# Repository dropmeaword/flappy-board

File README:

## Flappy board

(cc) 2017 Jelle Reith + Luis Rodil-Fernandez

Flappy board can be used to drive electromagnets for flappy textile projects.  :)

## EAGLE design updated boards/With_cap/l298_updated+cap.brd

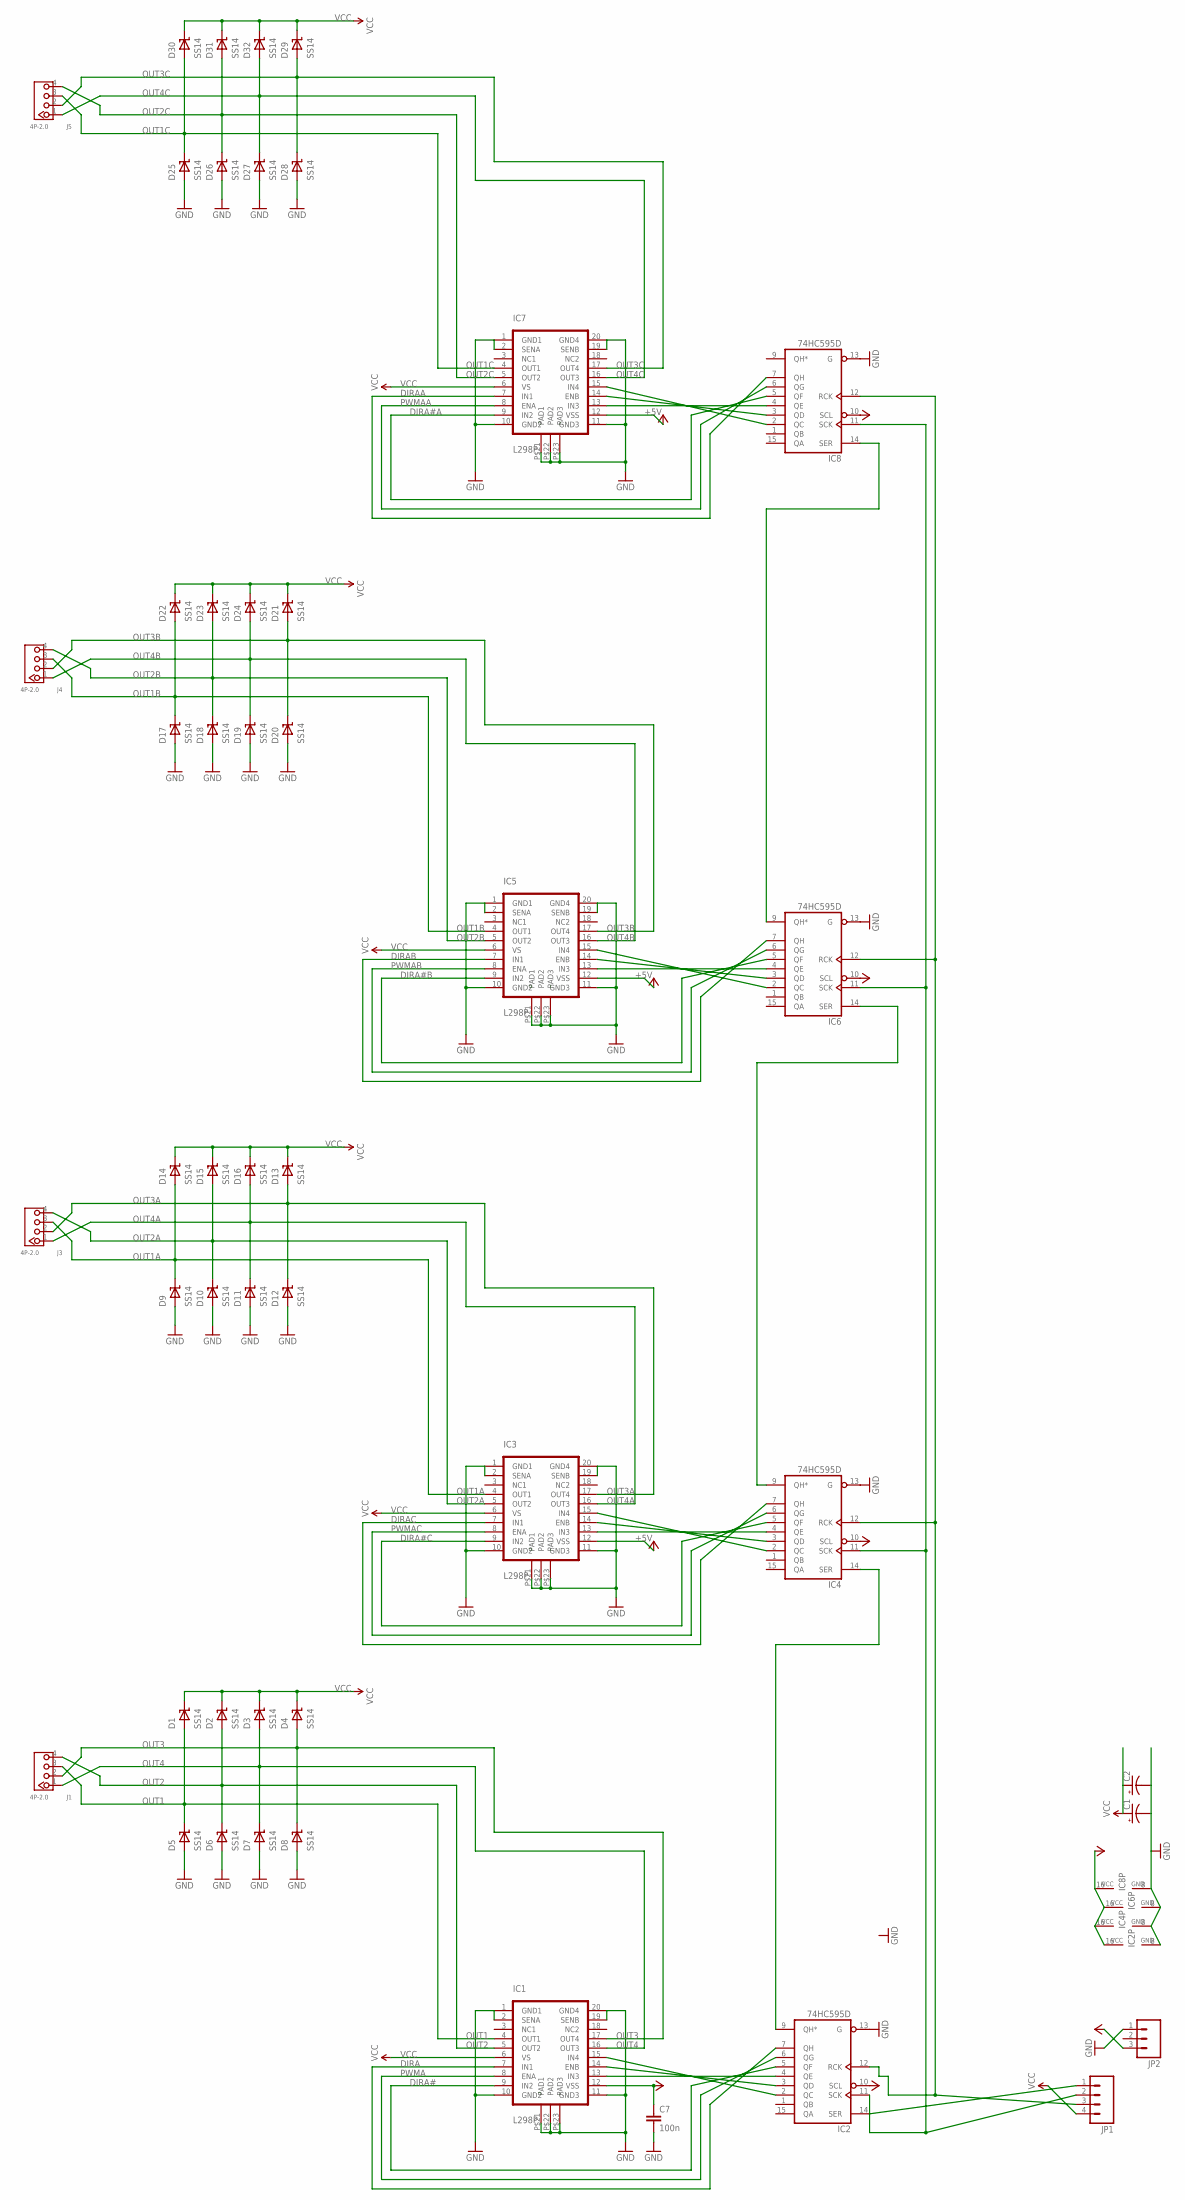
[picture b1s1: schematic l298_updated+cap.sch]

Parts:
C1: CAP_POL1206; EIA3216
C2: CAP_POL3528; EIA3528
C7: 100n; C0603-ROUND
D1, D2, D3, D4, D5, D6, D7, D8, D9, D10, D11, D12, D13, D14, D15, D16, D17, D18, D19, D20, D21, D22, D23, D24, D25, D26, D27, D28, D29, D30, D31, D32: SS14; SMA
IC1, IC3, IC5, IC7: L298P; POWER-SO20
IC2, IC4, IC6, IC8: 74HC595D; SO16
J1, J3, J4, J5: 4P-2.0; HW4-2.0
JP1: M04PTH; 1X04
JP2: M03PTH; 1X03

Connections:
+5V: C7.1, IC1.P$12 (VSS), IC2.10 (SCL), IC2.16 (VCC), IC3.P$12 (VSS), IC4.10 (SCL), IC4.16 (VCC), IC5.P$12 (VSS), IC6.10 (SCL), IC6.16 (VCC), IC7.P$12 (VSS), IC8.10 (SCL), IC8.16 (VCC), JP2.3
DIRA: IC1.P$7 (IN1), IC2.7 (QH)
DIRA#: IC1.P$9 (IN2), IC2.5 (QF)
DIRA#A: IC7.P$9 (IN2), IC8.5 (QF)
DIRA#B: IC5.P$9 (IN2), IC6.5 (QF)
DIRA#C: IC3.P$9 (IN2), IC4.5 (QF)
DIRAA: IC7.P$7 (IN1), IC8.7 (QH)
DIRAB: IC5.P$7 (IN1), IC6.7 (QH)
DIRAC: IC3.P$7 (IN1), IC4.7 (QH)
GND: C1.C (-), C2.C (-), C7.2, D5.P$2 (A), D6.P$2 (A), D7.P$2 (A), D8.P$2 (A), D9.P$2 (A), D10.P$2 (A), D11.P$2 (A), D12.P$2 (A), D17.P$2 (A), D18.P$2 (A), D19.P$2 (A), D20.P$2 (A), D25.P$2 (A), D26.P$2 (A), D27.P$2 (A), D28.P$2 (A), IC1.P$1 (GND1), IC1.P$2 (SENA), IC1.P$10 (GND2), IC1.P$11 (GND3), IC1.P$19 (SENB), IC1.P$20 (GND4), IC1.P$21 (PAD1), IC1.P$22 (PAD2), IC1.P$23 (PAD3), IC2.8 (GND), IC2.13 (G), IC3.P$1 (GND1), IC3.P$2 (SENA), IC3.P$10 (GND2), IC3.P$11 (GND3), IC3.P$19 (SENB), IC3.P$20 (GND4), IC3.P$21 (PAD1), IC3.P$22 (PAD2), IC3.P$23 (PAD3), IC4.8 (GND), IC4.13 (G), IC5.P$1 (GND1), IC5.P$2 (SENA), IC5.P$10 (GND2), IC5.P$11 (GND3), IC5.P$19 (SENB), IC5.P$20 (GND4), IC5.P$21 (PAD1), IC5.P$22 (PAD2), IC5.P$23 (PAD3), IC6.8 (GND), IC6.13 (G), IC7.P$1 (GND1), IC7.P$2 (SENA), IC7.P$10 (GND2), IC7.P$11 (GND3), IC7.P$19 (SENB), IC7.P$20 (GND4), IC7.P$21 (PAD1), IC7.P$22 (PAD2), IC7.P$23 (PAD3), IC8.8 (GND), IC8.13 (G), JP2.1
unnamed: IC2.9 (QH*), IC4.14 (SER)
unnamed: IC4.9 (QH*), IC6.14 (SER)
unnamed: IC6.9 (QH*), IC8.14 (SER)
unnamed: IC1.P$13 (IN3), IC2.4 (QE)
unnamed: IC1.P$14 (ENB), IC2.3 (QD)
unnamed: IC2.14 (SER), JP1.1
unnamed: IC2.11 (SCK), IC4.11 (SCK), IC6.11 (SCK), IC8.11 (SCK), JP1.2
unnamed: IC2.12 (RCK), IC4.12 (RCK), IC6.12 (RCK), IC8.12 (RCK), JP1.3
unnamed: IC1.P$15 (IN4), IC2.2 (QC)
unnamed: IC3.P$13 (IN3), IC4.4 (QE)
unnamed: IC3.P$14 (ENB), IC4.3 (QD)
unnamed: IC3.P$15 (IN4), IC4.2 (QC)
unnamed: IC5.P$13 (IN3), IC6.4 (QE)
unnamed: IC5.P$14 (ENB), IC6.3 (QD)
unnamed: IC5.P$15 (IN4), IC6.2 (QC)
unnamed: IC7.P$13 (IN3), IC8.4 (QE)
unnamed: IC7.P$14 (ENB), IC8.3 (QD)
unnamed: IC7.P$15 (IN4), IC8.2 (QC)
OUT1: D1.P$2 (A), D5.P$1 (K), IC1.P$4 (OUT1), J1.3
OUT1A: D9.P$1 (K), D14.P$2 (A), IC3.P$4 (OUT1), J3.3
OUT1B: D17.P$1 (K), D22.P$2 (A), IC5.P$4 (OUT1), J4.3
OUT1C: D25.P$1 (K), D30.P$2 (A), IC7.P$4 (OUT1), J5.3
OUT2: D2.P$2 (A), D6.P$1 (K), IC1.P$5 (OUT2), J1.4
OUT2A: D10.P$1 (K), D15.P$2 (A), IC3.P$5 (OUT2), J3.4
OUT2B: D18.P$1 (K), D23.P$2 (A), IC5.P$5 (OUT2), J4.4
OUT2C: D26.P$1 (K), D31.P$2 (A), IC7.P$5 (OUT2), J5.4
OUT3: D4.P$2 (A), D8.P$1 (K), IC1.P$17 (OUT4), J1.2
OUT3A: D12.P$1 (K), D13.P$2 (A), IC3.P$17 (OUT4), J3.2
OUT3B: D20.P$1 (K), D21.P$2 (A), IC5.P$17 (OUT4), J4.2
OUT3C: D28.P$1 (K), D29.P$2 (A), IC7.P$17 (OUT4), J5.2
OUT4: D3.P$2 (A), D7.P$1 (K), IC1.P$16 (OUT3), J1.1
OUT4A: D11.P$1 (K), D16.P$2 (A), IC3.P$16 (OUT3), J3.1
OUT4B: D19.P$1 (K), D24.P$2 (A), IC5.P$16 (OUT3), J4.1
OUT4C: D27.P$1 (K), D32.P$2 (A), IC7.P$16 (OUT3), J5.1
PWMA: IC1.P$8 (ENA), IC2.6 (QG)
PWMAA: IC7.P$8 (ENA), IC8.6 (QG)
PWMAB: IC5.P$8 (ENA), IC6.6 (QG)
PWMAC: IC3.P$8 (ENA), IC4.6 (QG)
VCC: C1.A (+), C2.A (+), D1.P$1 (K), D2.P$1 (K), D3.P$1 (K), D4.P$1 (K), D13.P$1 (K), D14.P$1 (K), D15.P$1 (K), D16.P$1 (K), D21.P$1 (K), D22.P$1 (K), D23.P$1 (K), D24.P$1 (K), D29.P$1 (K), D30.P$1 (K), D31.P$1 (K), D32.P$1 (K), IC1.P$6 (VS), IC3.P$6 (VS), IC5.P$6 (VS), IC7.P$6 (VS), JP1.4

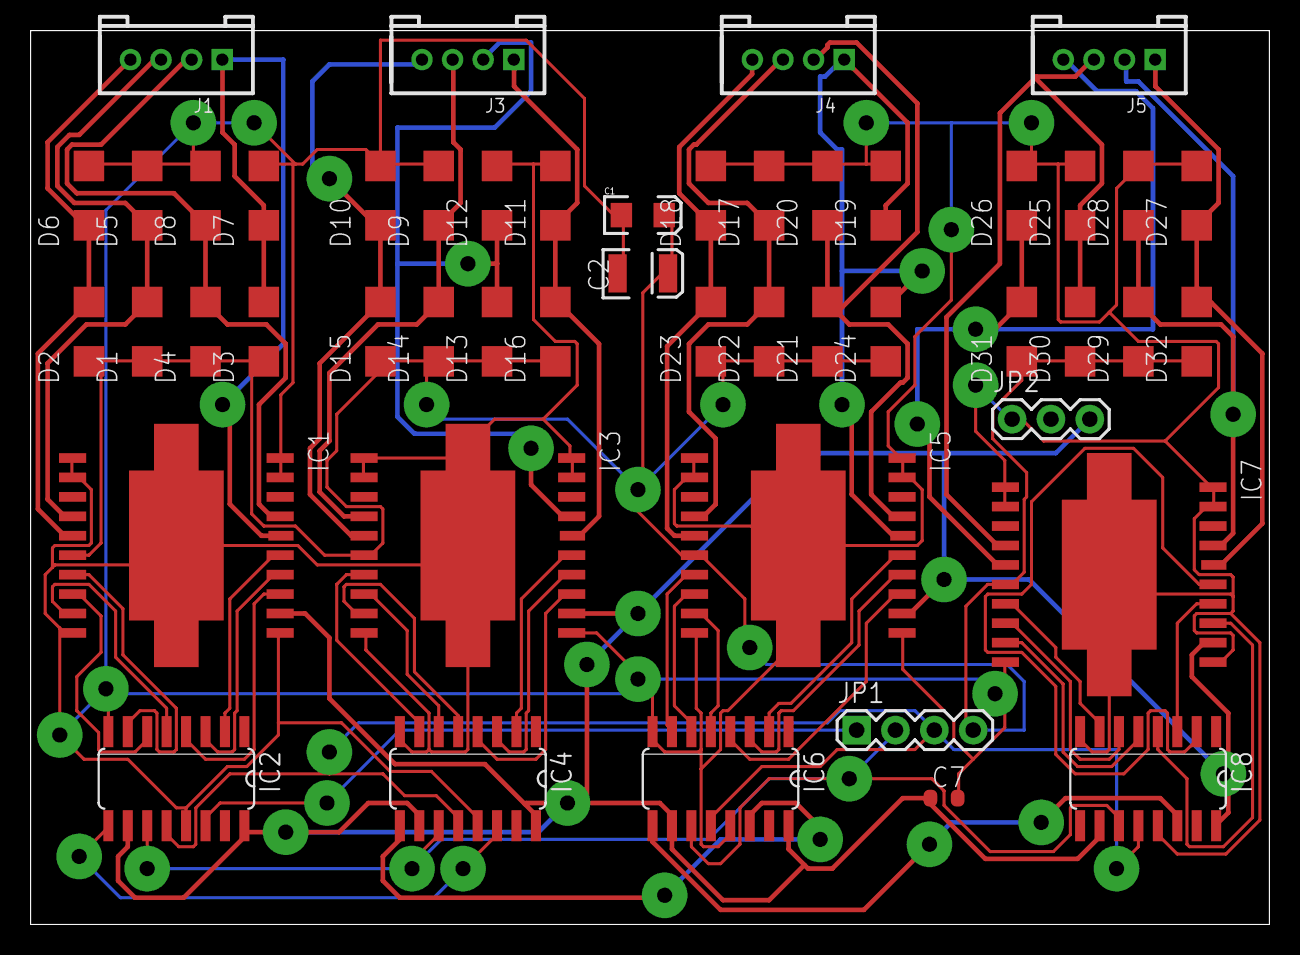
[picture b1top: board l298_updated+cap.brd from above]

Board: 2 copper layers, 81.0 x 58.4 mm, 49 parts (0 on the bottom side), 49 nets.

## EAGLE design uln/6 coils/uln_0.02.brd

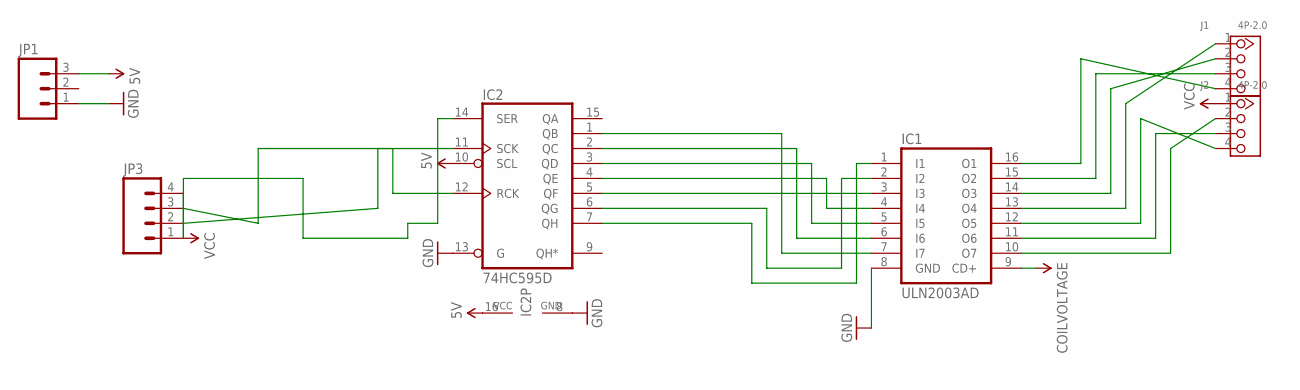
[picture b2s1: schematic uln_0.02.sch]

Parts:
IC1: ULN2003AD; SO16
IC2: 74HC595D; SO16
J1, J2: 4P-2.0; HW4-2.0
JP1: M03PTH; 1X03
JP3: M04PTH; 1X04

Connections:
5V: IC2.10 (SCL), IC2.16 (VCC), JP1.3
GND: IC1.8 (GND), IC2.8 (GND), IC2.13 (G), JP1.1
unnamed: IC1.7 (I7), IC2.1 (QB)
unnamed: IC1.6 (I6), IC2.2 (QC)
unnamed: IC1.5 (I5), IC2.3 (QD)
unnamed: IC1.4 (I4), IC2.4 (QE)
unnamed: IC1.3 (I3), IC2.5 (QF)
unnamed: IC1.2 (I2), IC2.6 (QG)
unnamed: IC1.1 (I1), IC2.7 (QH)
unnamed: IC1.10 (O7), J2.2
unnamed: IC1.11 (O6), J2.3
unnamed: IC1.12 (O5), J2.4
unnamed: IC1.13 (O4), J1.1
unnamed: IC1.14 (O3), J1.2
unnamed: IC1.15 (O2), J1.3
unnamed: IC1.16 (O1), J1.4
unnamed: IC2.11 (SCK), JP3.3
unnamed: IC2.12 (RCK), JP3.2
unnamed: IC2.14 (SER), JP3.1
VCC: IC1.9 (CD+), J2.1, JP3.4

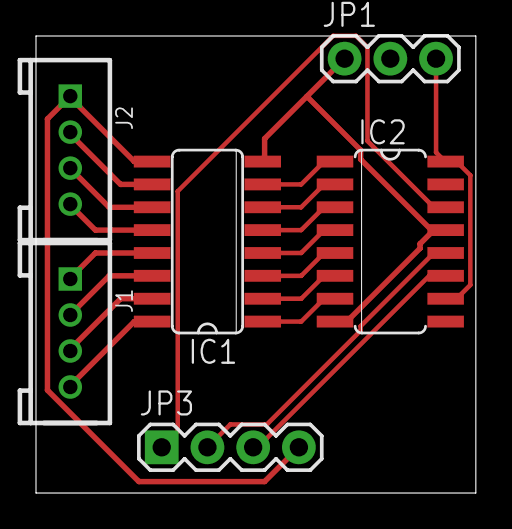
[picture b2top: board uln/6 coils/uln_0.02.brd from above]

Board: 2 copper layers, 24.4 x 25.4 mm, 6 parts (0 on the bottom side), 20 nets.

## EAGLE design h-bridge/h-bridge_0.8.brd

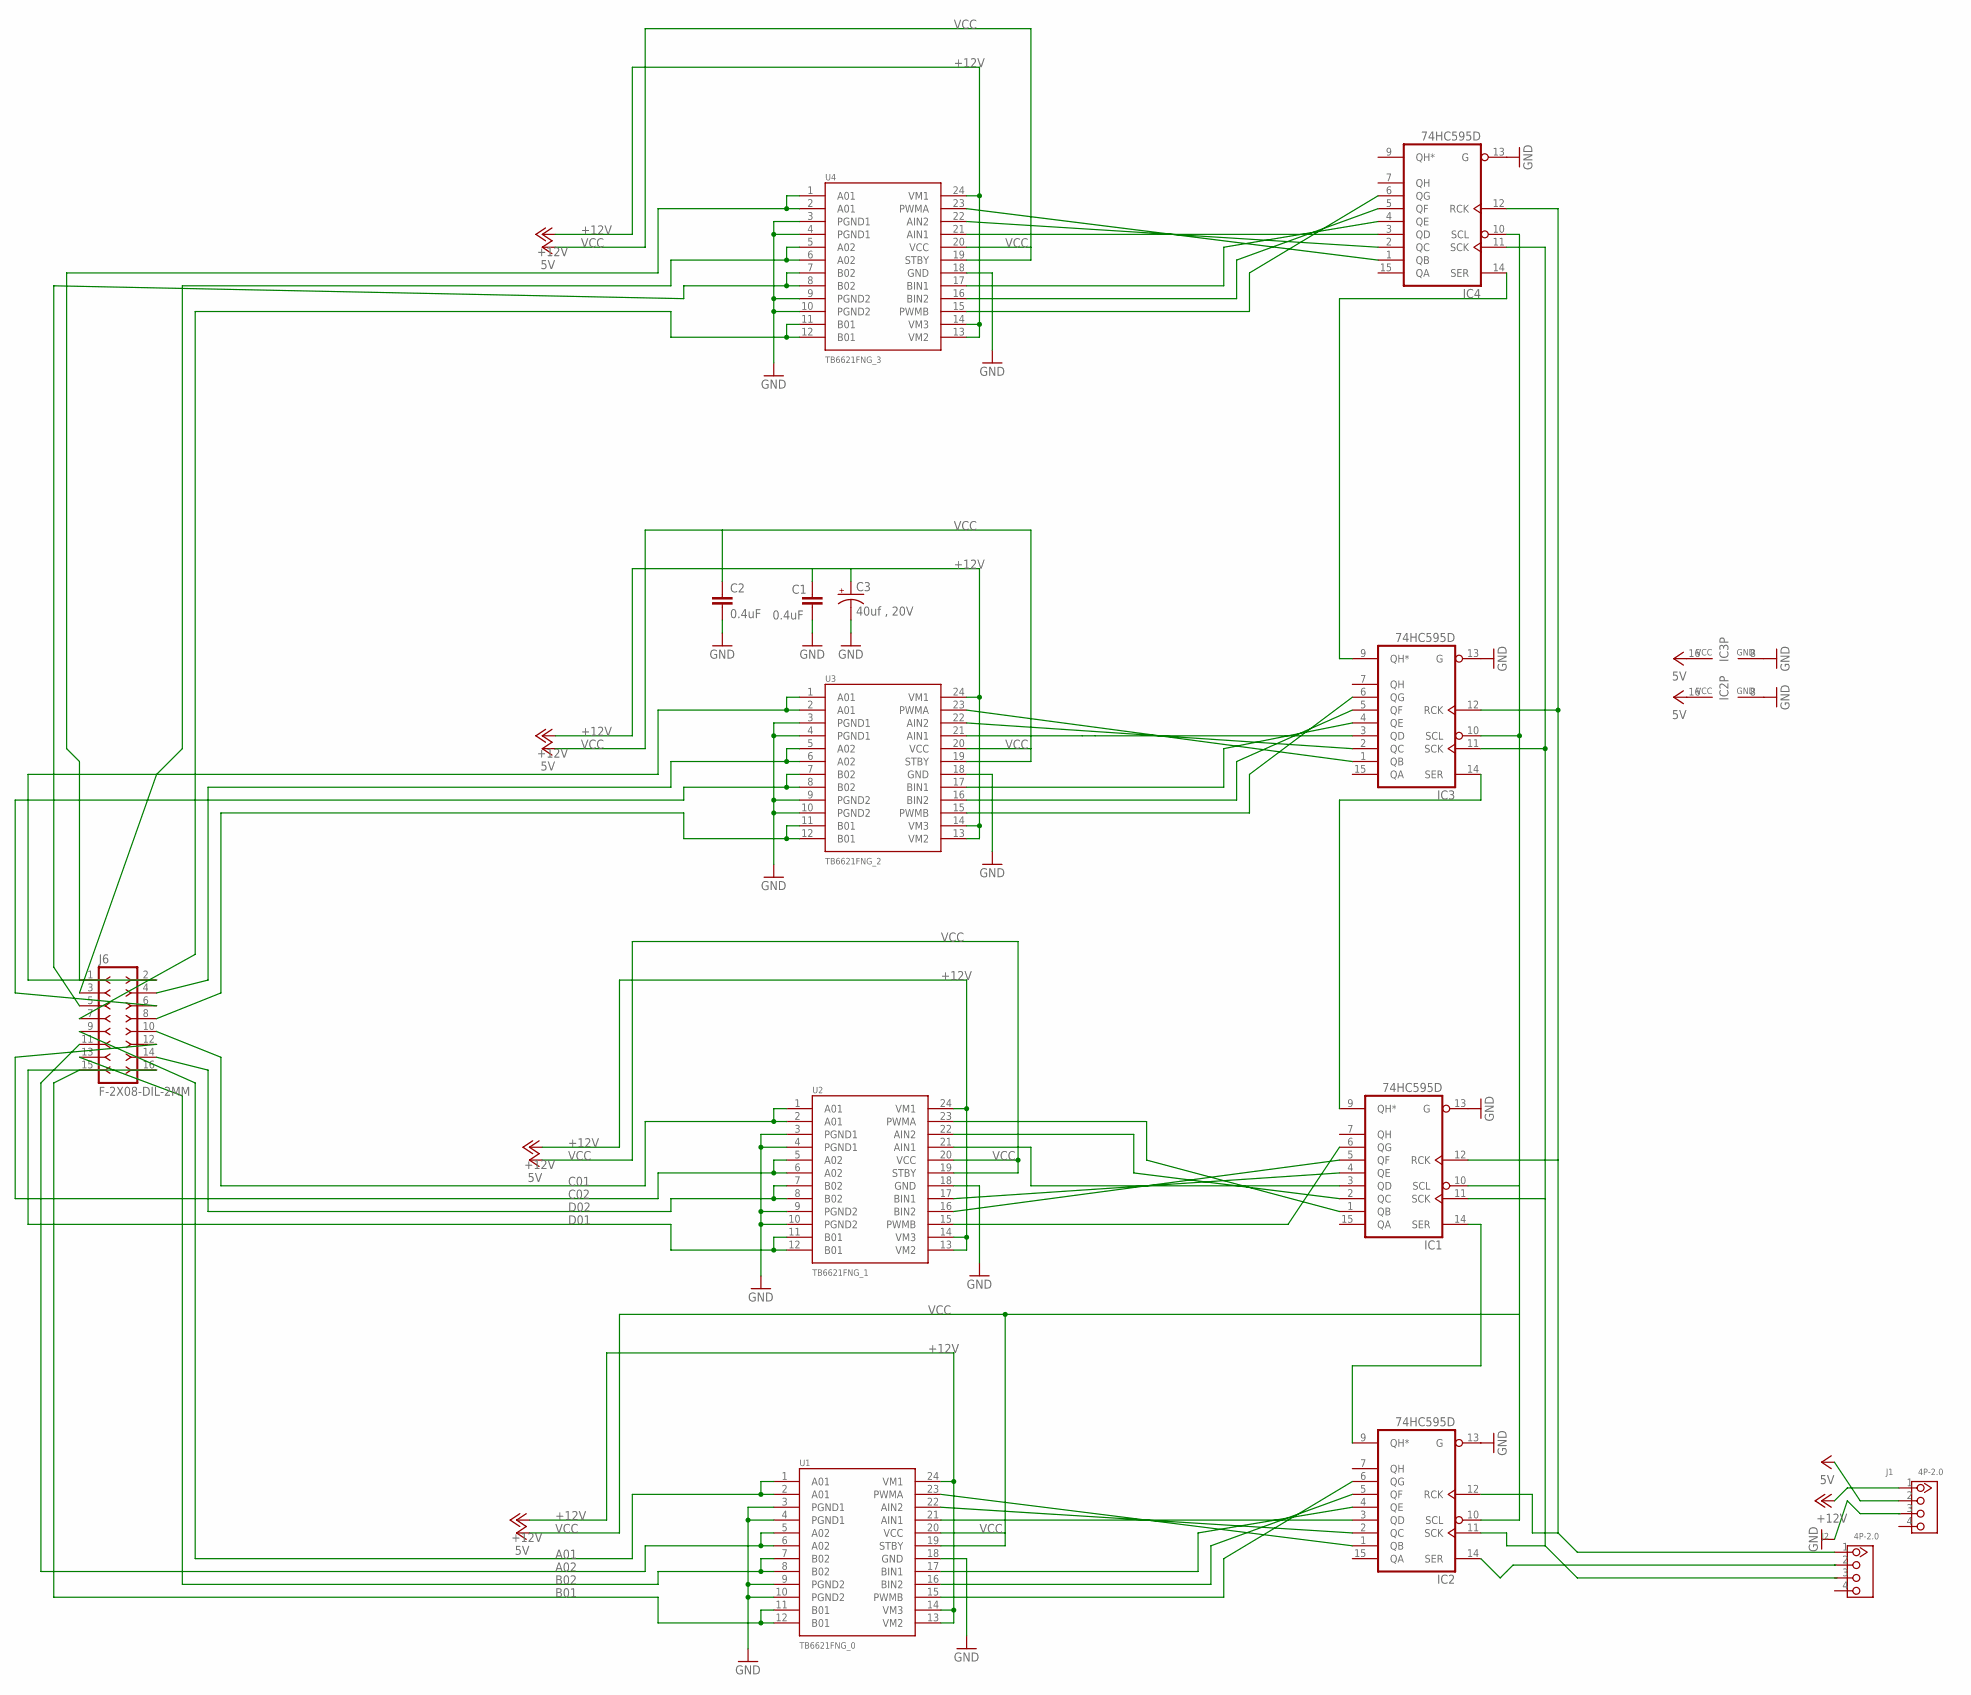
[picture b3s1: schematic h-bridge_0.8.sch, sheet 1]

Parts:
C1, C2: 0.4uF; 0402-CAP
C3: 40uf , 20V; EIA3528
IC1, IC2, IC3, IC4: 74HC595D; SO16
J1, J2: 4P-2.0; HW4-2.0
J6: F-2X08-DIL-2MM; DIL-2MM-2X08
U1: TB6621FNG_0; SSOP24
U2: TB6621FNG_1; SSOP24
U3: TB6621FNG_2; SSOP24
U4: TB6621FNG_3; SSOP24

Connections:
+12V: C1.1, C3.A (+), J1.1, U1.13 (VM2), U1.14 (VM3), U1.24 (VM1), U2.13 (VM2), U2.14 (VM3), U2.24 (VM1), U3.13 (VM2), U3.14 (VM3), U3.24 (VM1), U4.13 (VM2), U4.14 (VM3), U4.24 (VM1)
A01: J6.9, U1.1 (A01), U1.2 (A01)
A02: J6.11, U1.5 (A02), U1.6 (A02)
B01: J6.15, U1.11 (B01), U1.12 (B01)
B02: J6.13, U1.7 (B02), U1.8 (B02)
C01: J6.10, U2.1 (A01), U2.2 (A01)
C02: J6.12, U2.5 (A02), U2.6 (A02)
D01: J6.16, U2.11 (B01), U2.12 (B01)
D02: J6.14, U2.7 (B02), U2.8 (B02)
E01: J6.2, U3.1 (A01), U3.2 (A01)
E01A: J6.1, U4.1 (A01), U4.2 (A01)
E02: J6.4, U3.5 (A02), U3.6 (A02)
E02A: J6.5, U4.7 (B02), U4.8 (B02)
F01: J6.8, U3.11 (B01), U3.12 (B01)
F01A: J6.7, U4.11 (B01), U4.12 (B01)
F02: J6.6, U3.7 (B02), U3.8 (B02)
F02A: J6.3, U4.5 (A02), U4.6 (A02)
GND: C1.2, C2.2, C3.C (-), IC1.8 (GND), IC1.13 (G), IC2.8 (GND), IC2.13 (G), IC3.8 (GND), IC3.13 (G), IC4.8 (GND), IC4.13 (G), J1.3, U1.3 (PGND1), U1.4 (PGND1), U1.9 (PGND2), U1.10 (PGND2), U1.18 (GND), U2.3 (PGND1), U2.4 (PGND1), U2.9 (PGND2), U2.10 (PGND2), U2.18 (GND), U3.3 (PGND1), U3.4 (PGND1), U3.9 (PGND2), U3.10 (PGND2), U3.18 (GND), U4.3 (PGND1), U4.4 (PGND1), U4.9 (PGND2), U4.10 (PGND2), U4.18 (GND)
unnamed: IC2.5 (QF), U1.16 (BIN2)
unnamed: IC3.5 (QF), U3.16 (BIN2)
unnamed: IC2.2 (QC), U1.22 (AIN2)
unnamed: IC3.4 (QE), U3.17 (BIN1)
unnamed: IC2.6 (QG), U1.15 (PWMB)
unnamed: IC2.1 (QB), U1.23 (PWMA)
unnamed: IC2.14 (SER), J2.2
unnamed: IC1.14 (SER), IC2.9 (QH*)
unnamed: IC2.4 (QE), U1.17 (BIN1)
unnamed: IC1.6 (QG), U2.15 (PWMB)
unnamed: IC2.3 (QD), U1.21 (AIN1)
unnamed: IC1.5 (QF), U2.16 (BIN2)
unnamed: IC1.4 (QE), U2.17 (BIN1)
unnamed: IC1.3 (QD), U2.21 (AIN1)
unnamed: IC1.2 (QC), U2.22 (AIN2)
unnamed: IC1.9 (QH*), IC3.14 (SER)
unnamed: IC1.1 (QB), U2.23 (PWMA)
unnamed: IC3.3 (QD), U3.21 (AIN1)
unnamed: IC3.6 (QG), U3.15 (PWMB)
unnamed: IC3.2 (QC), U3.22 (AIN2)
unnamed: IC3.1 (QB), U3.23 (PWMA)
unnamed: IC1.11 (SCK), IC2.11 (SCK), IC3.11 (SCK), IC4.11 (SCK)
unnamed: IC1.12 (RCK), IC2.12 (RCK), IC3.12 (RCK), IC4.12 (RCK), J2.1
unnamed: IC4.6 (QG), U4.15 (PWMB)
unnamed: IC3.9 (QH*), IC4.14 (SER)
unnamed: IC4.5 (QF), U4.16 (BIN2)
unnamed: IC4.4 (QE), U4.17 (BIN1)
unnamed: IC4.3 (QD), U4.21 (AIN1)
unnamed: IC4.2 (QC), U4.22 (AIN2)
unnamed: IC4.1 (QB), U4.23 (PWMA)
VCC: C2.1, IC1.10 (SCL), IC1.16 (VCC), IC2.10 (SCL), IC2.16 (VCC), IC3.10 (SCL), IC3.16 (VCC), IC4.10 (SCL), IC4.16 (VCC), J1.2, U1.19 (STBY), U1.20 (VCC), U2.19 (STBY), U2.20 (VCC), U3.19 (STBY), U3.20 (VCC), U4.19 (STBY), U4.20 (VCC)

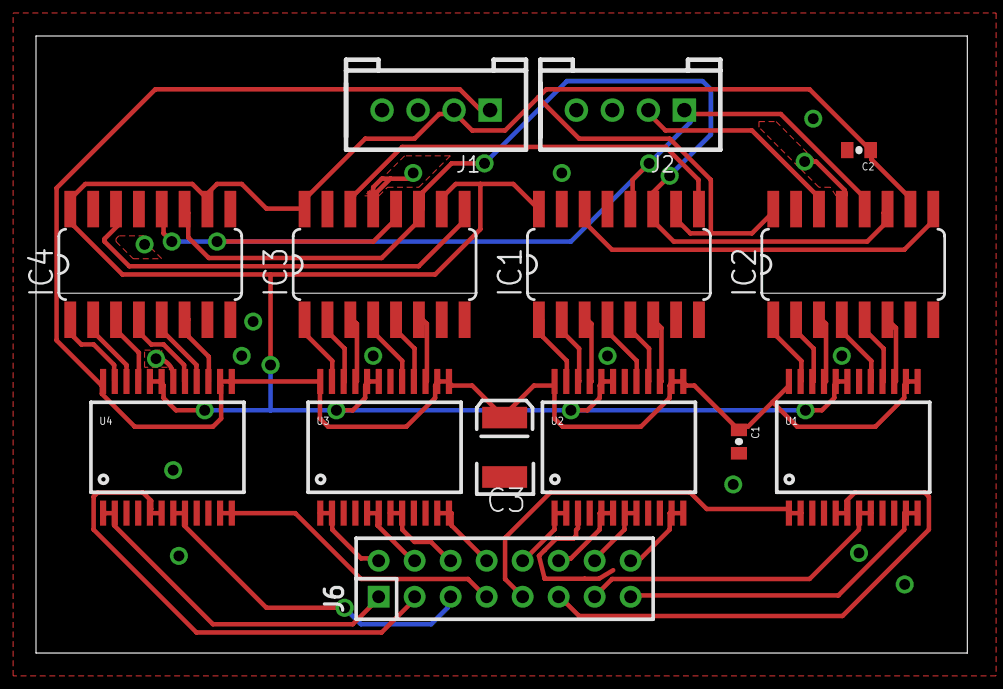
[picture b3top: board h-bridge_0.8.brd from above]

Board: 2 copper layers, 51.7 x 34.3 mm, 14 parts (0 on the bottom side), 49 nets.

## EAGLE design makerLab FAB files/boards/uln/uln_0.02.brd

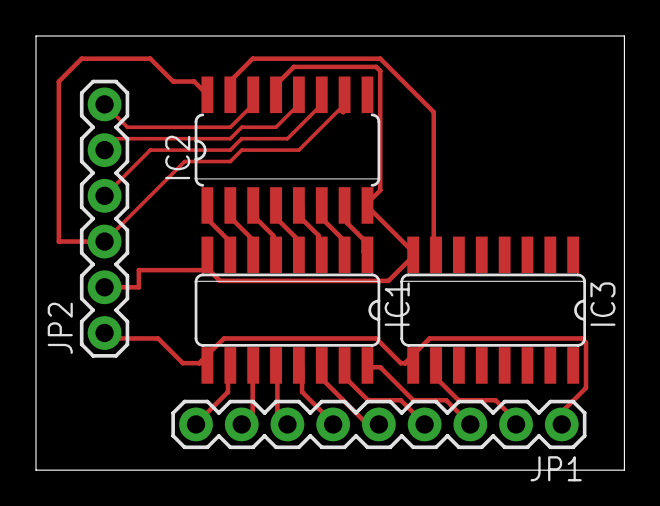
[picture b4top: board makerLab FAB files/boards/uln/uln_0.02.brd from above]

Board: 2 copper layers, 32.7 x 24.1 mm, 5 parts (0 on the bottom side), 22 nets.

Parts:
IC1, IC3: ULN2003AD; SO16
IC2: 74HC595D; SO16
JP1: M09; 1X09
JP2: 1X06

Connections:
5V: IC2.10, IC2.16, JP2.3
GND: IC1.8, IC2.8, IC2.13, IC3.8, JP2.2
unnamed: IC1.7, IC2.1
unnamed: IC1.6, IC2.2
unnamed: IC1.5, IC2.3
unnamed: IC1.4, IC2.4
unnamed: IC1.3, IC2.5
unnamed: IC1.2, IC2.6
unnamed: IC1.1, IC2.7
unnamed: IC2.15, IC3.7
unnamed: IC1.10, JP1.9
unnamed: IC1.11, JP1.8
unnamed: IC1.12, JP1.7
unnamed: IC1.13, JP1.6
unnamed: IC1.14, JP1.5
unnamed: IC1.15, JP1.4
unnamed: IC1.16, JP1.3
unnamed: IC3.10, JP1.2
unnamed: IC2.11, JP2.4
unnamed: IC2.12, JP2.5
unnamed: IC2.14, JP2.6
VCC: IC1.9, IC3.9, JP1.1, JP2.1

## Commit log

2017-02-16 updated .gitignore
2017-02-16 README
2017-02-16 renamed README file
2017-02-16 added EAGLE design rules for DRC check
2017-02-17 added the EAGLE DRC rules and documented the ULN board
2017-02-17 i just added this file
2017-02-17 added a small PD patch that sends beat data to the featherboard
2017-02-20 Package size of h-bridges
    Left a single h-bridge
    Right a double h-bridge
2017-03-03 Updated uln2003 and l298 board
    Last version ;)
    Ready to be made at the hva lab
2017-03-06 Just a safety cap

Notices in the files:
parts and their libraries:
con-headers-jp: Copyright (C) 2008, Bob Starr
